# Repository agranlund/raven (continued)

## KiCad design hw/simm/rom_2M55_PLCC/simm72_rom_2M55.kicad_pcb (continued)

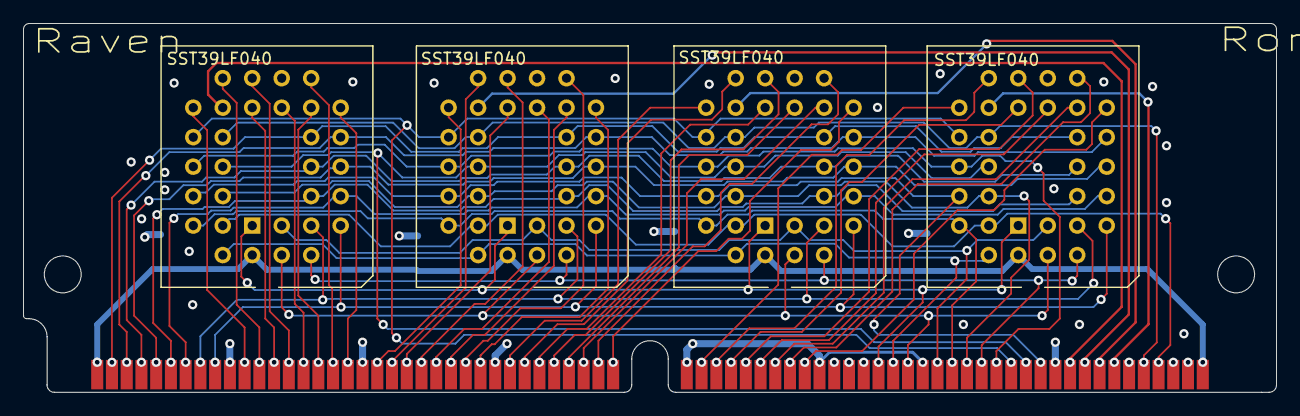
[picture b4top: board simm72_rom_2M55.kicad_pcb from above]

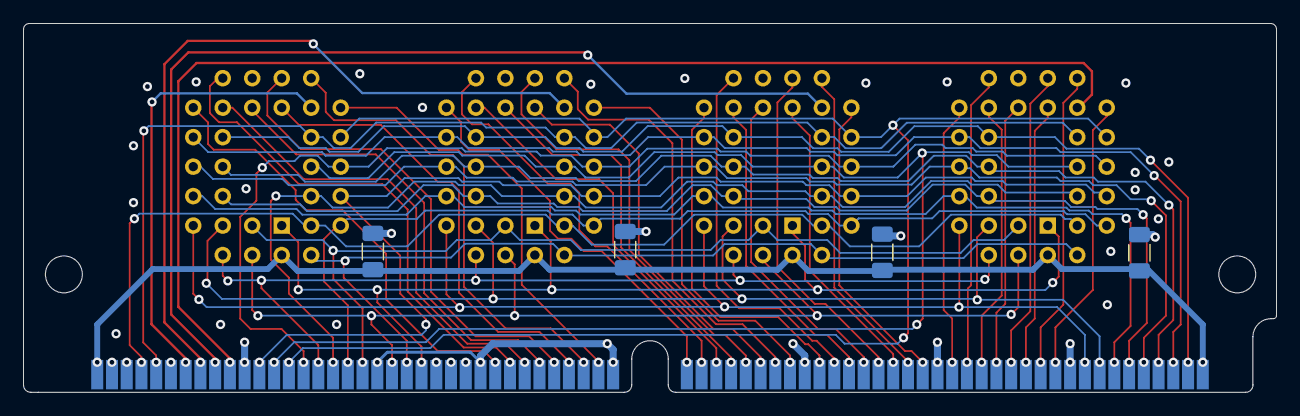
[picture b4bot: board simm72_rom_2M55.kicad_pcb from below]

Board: 4 copper layers, 108.0 x 31.8 mm, 9 parts (4 on the bottom side), 59 nets.

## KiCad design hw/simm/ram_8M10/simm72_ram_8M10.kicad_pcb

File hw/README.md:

All PCBs are designed within JLCPCB tolerances and Gerbers are exported for JLCPCB specifications.

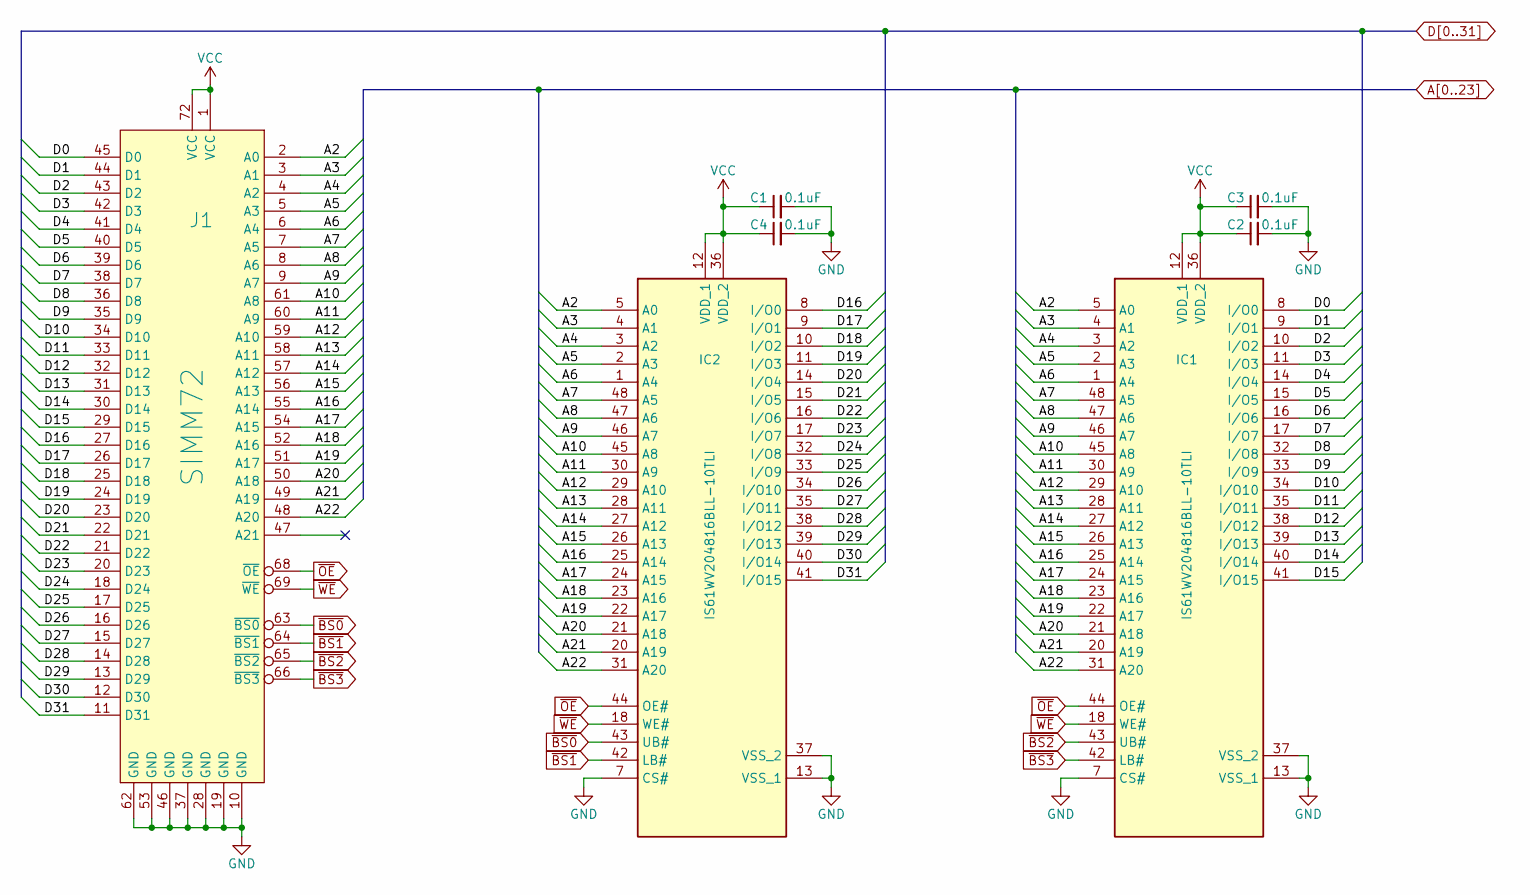
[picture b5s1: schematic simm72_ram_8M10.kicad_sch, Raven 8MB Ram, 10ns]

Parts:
C1, C2, C3, C4: 0.1uF; C_1206_3216Metric_Pad1.33x1.80mm_HandSolder; Manufacturer_Part_Number C1206C104K5RACTU
IC1, IC2: IS61WV204816BLL-10TLI; SOP50P2000X120-48N; Mouser Part Number 870-WV204816BLL10TLI
J1: SIMM72; SIMM72_edge

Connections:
A2: IC1.5 (A0), IC2.5 (A0), J1.2 (A0)
A3: IC1.4 (A1), IC2.4 (A1), J1.3 (A1)
A4: IC1.3 (A2), IC2.3 (A2), J1.4 (A2)
A5: IC1.2 (A3), IC2.2 (A3), J1.5 (A3)
A6: IC1.1 (A4), IC2.1 (A4), J1.6 (A4)
A7: IC1.48 (A5), IC2.48 (A5), J1.7 (A5)
A8: IC1.47 (A6), IC2.47 (A6), J1.8 (A6)
A9: IC1.46 (A7), IC2.46 (A7), J1.9 (A7)
A10: IC1.45 (A8), IC2.45 (A8), J1.61 (A8)
A11: IC1.30 (A9), IC2.30 (A9), J1.60 (A9)
A12: IC1.29 (A10), IC2.29 (A10), J1.59 (A10)
A13: IC1.28 (A11), IC2.28 (A11), J1.58 (A11)
A14: IC1.27 (A12), IC2.27 (A12), J1.57 (A12)
A15: IC1.26 (A13), IC2.26 (A13), J1.56 (A13)
A16: IC1.25 (A14), IC2.25 (A14), J1.55 (A14)
A17: IC1.24 (A15), IC2.24 (A15), J1.54 (A15)
A18: IC1.23 (A16), IC2.23 (A16), J1.52 (A16)
A19: IC1.22 (A17), IC2.22 (A17), J1.51 (A17)
A20: IC1.21 (A18), IC2.21 (A18), J1.50 (A18)
A21: IC1.20 (A19), IC2.20 (A19), J1.49 (A19)
A22: IC1.31 (A20), IC2.31 (A20), J1.48 (A20)
D0: IC1.8 (I/O0), J1.45 (D0)
D1: IC1.9 (I/O1), J1.44 (D1)
D2: IC1.10 (I/O2), J1.43 (D2)
D3: IC1.11 (I/O3), J1.42 (D3)
D4: IC1.14 (I/O4), J1.41 (D4)
D5: IC1.15 (I/O5), J1.40 (D5)
D6: IC1.16 (I/O6), J1.39 (D6)
D7: IC1.17 (I/O7), J1.38 (D7)
D8: IC1.32 (I/O8), J1.36 (D8)
D9: IC1.33 (I/O9), J1.35 (D9)
D10: IC1.34 (I/O10), J1.34 (D10)
D11: IC1.35 (I/O11), J1.33 (D11)
D12: IC1.38 (I/O12), J1.32 (D12)
D13: IC1.39 (I/O13), J1.31 (D13)
D14: IC1.40 (I/O14), J1.30 (D14)
D15: IC1.41 (I/O15), J1.29 (D15)
D16: IC2.8 (I/O0), J1.27 (D16)
D17: IC2.9 (I/O1), J1.26 (D17)
D18: IC2.10 (I/O2), J1.25 (D18)
D19: IC2.11 (I/O3), J1.24 (D19)
D20: IC2.14 (I/O4), J1.23 (D20)
D21: IC2.15 (I/O5), J1.22 (D21)
D22: IC2.16 (I/O6), J1.21 (D22)
D23: IC2.17 (I/O7), J1.20 (D23)
D24: IC2.32 (I/O8), J1.18 (D24)
D25: IC2.33 (I/O9), J1.17 (D25)
D26: IC2.34 (I/O10), J1.16 (D26)
D27: IC2.35 (I/O11), J1.15 (D27)
D28: IC2.38 (I/O12), J1.14 (D28)
D29: IC2.39 (I/O13), J1.13 (D29)
D30: IC2.40 (I/O14), J1.12 (D30)
D31: IC2.41 (I/O15), J1.11 (D31)
GND: C1.2, C2.2, C3.2, C4.2, IC1.7 (CS#), IC1.13 (VSS_1), IC1.37 (VSS_2), IC2.7 (CS#), IC2.13 (VSS_1), IC2.37 (VSS_2), J1.10 (GND), J1.19 (GND), J1.28 (GND), J1.37 (GND), J1.46 (GND), J1.53 (GND), J1.62 (GND)
VCC: C1.1, C2.1, C3.1, C4.1, IC1.12 (VDD_1), IC1.36 (VDD_2), IC2.12 (VDD_1), IC2.36 (VDD_2), J1.1 (VCC), J1.72 (VCC)
~BS0: IC2.43 (UB#), J1.63 (~BS0)
~BS1: IC2.42 (LB#), J1.64 (~BS1)
~BS2: IC1.43 (UB#), J1.65 (~BS2)
~BS3: IC1.42 (LB#), J1.66 (~BS3)
~OE: IC1.44 (OE#), IC2.44 (OE#), J1.68 (~OE)
~WE: IC1.18 (WE#), IC2.18 (WE#), J1.69 (~WE)

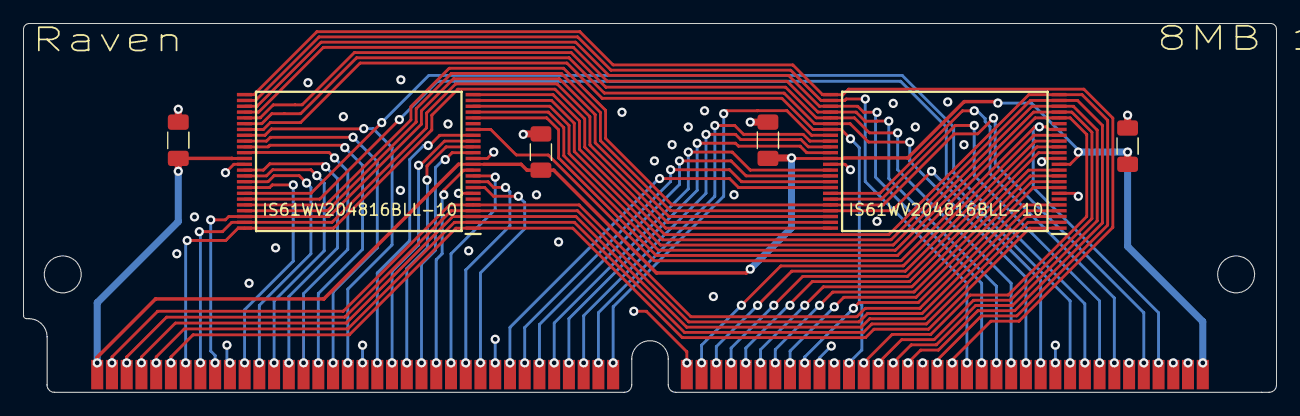
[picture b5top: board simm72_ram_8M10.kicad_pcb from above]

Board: 4 copper layers, 108.0 x 31.8 mm, 7 parts (0 on the bottom side), 61 nets.

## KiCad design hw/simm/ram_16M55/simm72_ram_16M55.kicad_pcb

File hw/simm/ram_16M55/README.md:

# RAM module: 16MB / 55ns

## BOM

| Manufacturer          | Part number                 | Value       | Count | Ref                                   |
|-----------------------|-----------------------------|-------------|-------|---------------------------------------|
| Alliance Memory       | AS6C6416-55TIN              | 16x4MBit    | 2     | IC1, IC2                              |
| Kemet                 | C1206C104K5RACTU            | 0.1u        | 2     | C1, C2                                |

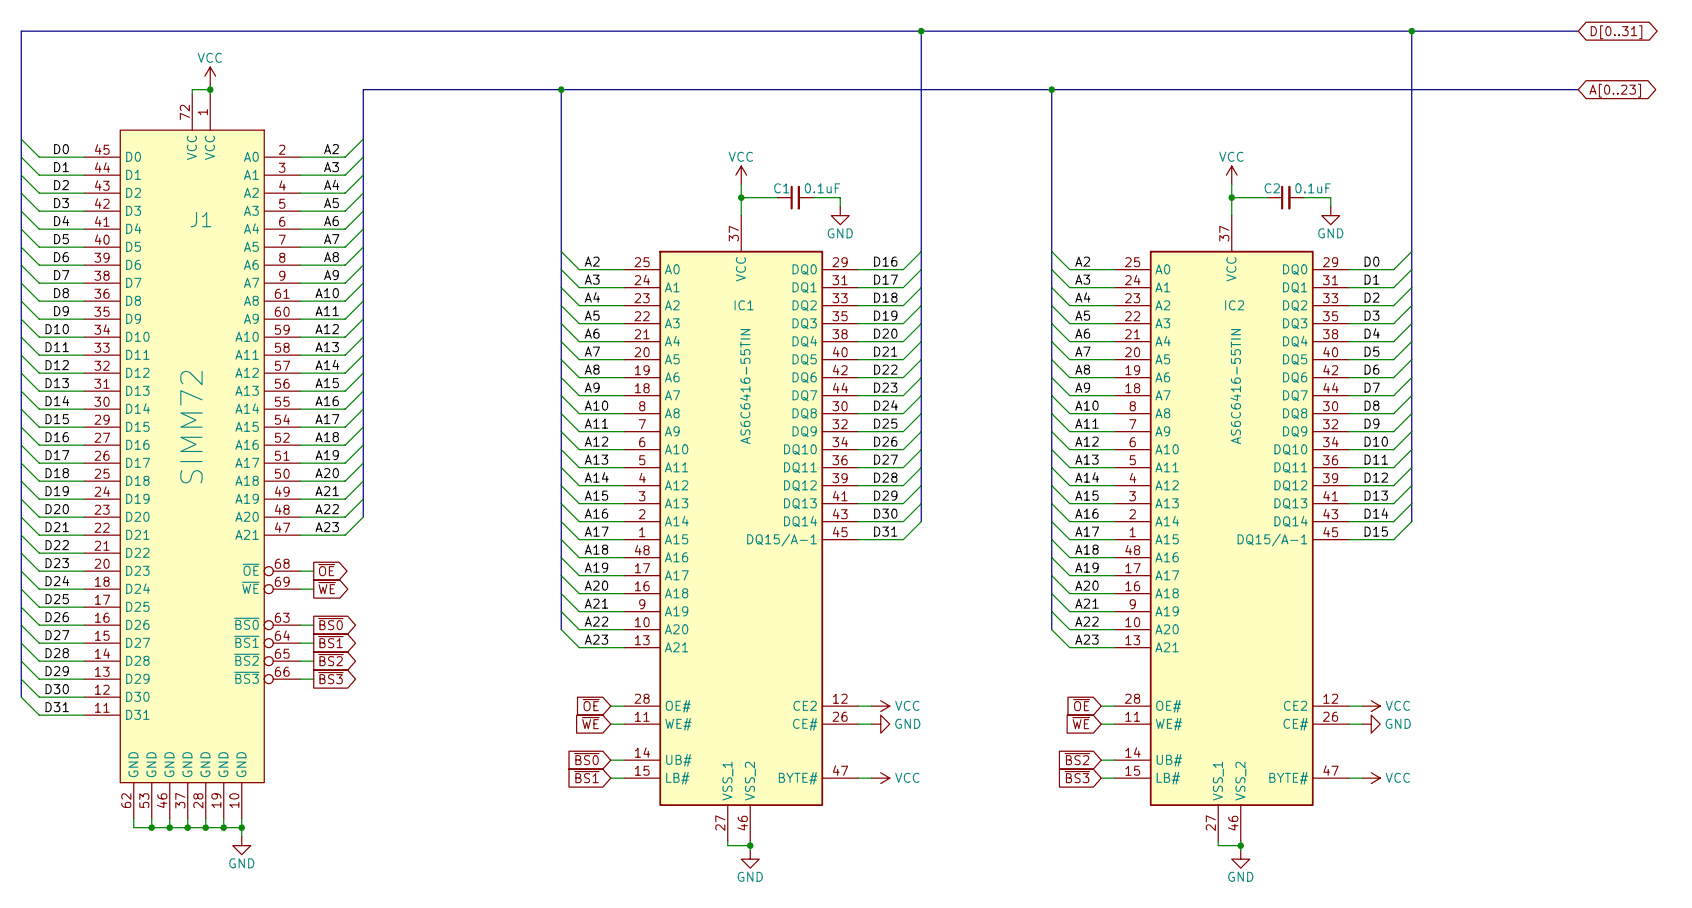
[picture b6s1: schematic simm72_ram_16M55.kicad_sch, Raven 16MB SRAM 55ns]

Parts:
C1, C2: 0.1uF; C_1206_3216Metric_Pad1.33x1.80mm_HandSolder; Manufacturer_Part_Number C1206C104K5RACTU
IC1, IC2: AS6C6416-55TIN; SOP50P2000X120-48N; Mouser Part Number 913-AS6C6416-55TIN
J1: SIMM72; SIMM72_edge

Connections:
A2: IC1.25 (A0), IC2.25 (A0), J1.2 (A0)
A3: IC1.24 (A1), IC2.24 (A1), J1.3 (A1)
A4: IC1.23 (A2), IC2.23 (A2), J1.4 (A2)
A5: IC1.22 (A3), IC2.22 (A3), J1.5 (A3)
A6: IC1.21 (A4), IC2.21 (A4), J1.6 (A4)
A7: IC1.20 (A5), IC2.20 (A5), J1.7 (A5)
A8: IC1.19 (A6), IC2.19 (A6), J1.8 (A6)
A9: IC1.18 (A7), IC2.18 (A7), J1.9 (A7)
A10: IC1.8 (A8), IC2.8 (A8), J1.61 (A8)
A11: IC1.7 (A9), IC2.7 (A9), J1.60 (A9)
A12: IC1.6 (A10), IC2.6 (A10), J1.59 (A10)
A13: IC1.5 (A11), IC2.5 (A11), J1.58 (A11)
A14: IC1.4 (A12), IC2.4 (A12), J1.57 (A12)
A15: IC1.3 (A13), IC2.3 (A13), J1.56 (A13)
A16: IC1.2 (A14), IC2.2 (A14), J1.55 (A14)
A17: IC1.1 (A15), IC2.1 (A15), J1.54 (A15)
A18: IC1.48 (A16), IC2.48 (A16), J1.52 (A16)
A19: IC1.17 (A17), IC2.17 (A17), J1.51 (A17)
A20: IC1.16 (A18), IC2.16 (A18), J1.50 (A18)
A21: IC1.9 (A19), IC2.9 (A19), J1.49 (A19)
A22: IC1.10 (A20), IC2.10 (A20), J1.48 (A20)
A23: IC1.13 (A21), IC2.13 (A21), J1.47 (A21)
D0: IC2.29 (DQ0), J1.45 (D0)
D1: IC2.31 (DQ1), J1.44 (D1)
D2: IC2.33 (DQ2), J1.43 (D2)
D3: IC2.35 (DQ3), J1.42 (D3)
D4: IC2.38 (DQ4), J1.41 (D4)
D5: IC2.40 (DQ5), J1.40 (D5)
D6: IC2.42 (DQ6), J1.39 (D6)
D7: IC2.44 (DQ7), J1.38 (D7)
D8: IC2.30 (DQ8), J1.36 (D8)
D9: IC2.32 (DQ9), J1.35 (D9)
D10: IC2.34 (DQ10), J1.34 (D10)
D11: IC2.36 (DQ11), J1.33 (D11)
D12: IC2.39 (DQ12), J1.32 (D12)
D13: IC2.41 (DQ13), J1.31 (D13)
D14: IC2.43 (DQ14), J1.30 (D14)
D15: IC2.45 (DQ15/A-1), J1.29 (D15)
D16: IC1.29 (DQ0), J1.27 (D16)
D17: IC1.31 (DQ1), J1.26 (D17)
D18: IC1.33 (DQ2), J1.25 (D18)
D19: IC1.35 (DQ3), J1.24 (D19)
D20: IC1.38 (DQ4), J1.23 (D20)
D21: IC1.40 (DQ5), J1.22 (D21)
D22: IC1.42 (DQ6), J1.21 (D22)
D23: IC1.44 (DQ7), J1.20 (D23)
D24: IC1.30 (DQ8), J1.18 (D24)
D25: IC1.32 (DQ9), J1.17 (D25)
D26: IC1.34 (DQ10), J1.16 (D26)
D27: IC1.36 (DQ11), J1.15 (D27)
D28: IC1.39 (DQ12), J1.14 (D28)
D29: IC1.41 (DQ13), J1.13 (D29)
D30: IC1.43 (DQ14), J1.12 (D30)
D31: IC1.45 (DQ15/A-1), J1.11 (D31)
GND: C1.2, C2.2, IC1.26 (CE#), IC1.27 (VSS_1), IC1.46 (VSS_2), IC2.26 (CE#), IC2.27 (VSS_1), IC2.46 (VSS_2), J1.10 (GND), J1.19 (GND), J1.28 (GND), J1.37 (GND), J1.46 (GND), J1.53 (GND), J1.62 (GND)
VCC: C1.1, C2.1, IC1.12 (CE2), IC1.37 (VCC), IC1.47 (BYTE#), IC2.12 (CE2), IC2.37 (VCC), IC2.47 (BYTE#), J1.1 (VCC), J1.72 (VCC)
~BS0: IC1.14 (UB#), J1.63 (~BS0)
~BS1: IC1.15 (LB#), J1.64 (~BS1)
~BS2: IC2.14 (UB#), J1.65 (~BS2)
~BS3: IC2.15 (LB#), J1.66 (~BS3)
~OE: IC1.28 (OE#), IC2.28 (OE#), J1.68 (~OE)
~WE: IC1.11 (WE#), IC2.11 (WE#), J1.69 (~WE)

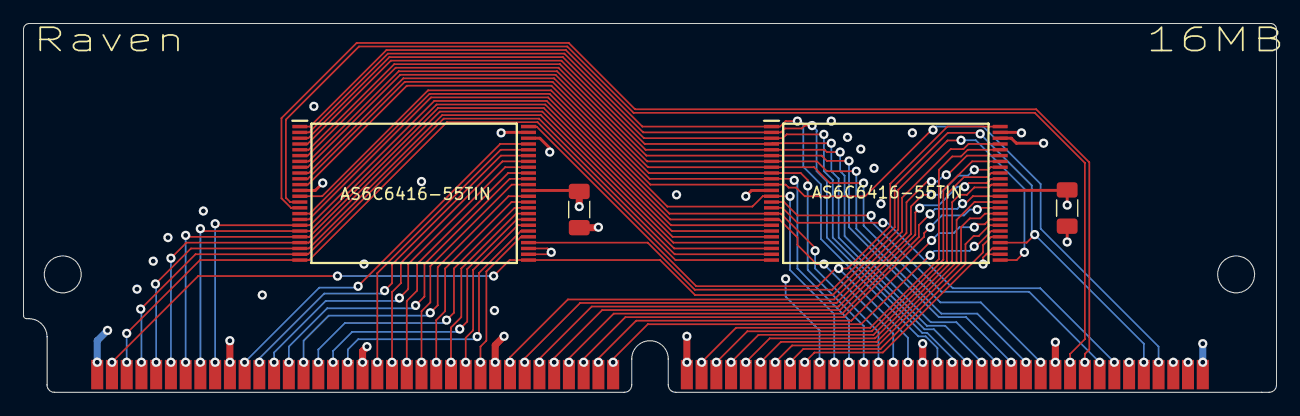
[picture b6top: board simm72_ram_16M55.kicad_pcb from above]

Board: 4 copper layers, 108.0 x 31.8 mm, 5 parts (0 on the bottom side), 62 nets.

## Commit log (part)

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2026-02-14 debugprint refactor
2026-02-14 rvnova tools
2026-02-14 tiny cleanups
2026-02-14 Update ISA graphics card requirements in README
    Expanded ISA graphics card section with hardware acceleration details.
2026-02-14 Create makefile
2026-02-15 rvnova settings
    - added rvga.inf settings file
    - remove w32i interleave option from rvbios
    - rename default driver to svga
    - use generated bibs for svga driver
2026-02-15 setaddr fix for < GD5426
2026-02-15 fix compile error in debug
2026-02-15 wip tseng driver (disabled)
2026-02-15 wip tseng driver enabled
2026-02-15 v_bar vdi accel can now compile again
    did some tests, still not working in 100% scenarios. keep disabled.
2026-02-16 Add Blender 3D IO Shield file
    add Blender 3D file used to create IO Shield STL
2026-02-16 tseng fixes
    - correctly place W32i LFB address
    - detect clocks for custom resolutions
    - 1280x720 works and tested on AX and W32i
2026-02-17 tseng: use vgabios to set refresh rate when supported
2026-02-17 rvnova : accelerate v_bar primitive
2026-02-18 hardware accelerate vt_clear_rows
2026-02-23 rvga: build for 020+
2026-02-23 WDC reduce blitter call overhead
2026-02-23 Cirrus: reduce blitter call overhead
    - reduce redundant register writes
    - use mmio on GD5429+
    - use polyfill capabilities on GD5429+
2026-02-23 additional vdi acceleration
    - vt52 clear rows
    - general VDI primitives accelerated with naive blitter hlines
2026-02-23 cirrus: pattern fill fix
2026-02-23 remove a bunch of temp comments
2026-02-25 don't force 8x8 terminal font
    was causing issues with nova vdi
2026-02-25 wip trapezoid testing
2026-02-25 Update graphics card hardware acceleration details
2026-02-28 cirrus: fixed bad pattern address
    was setting wrong address on gpu side.
    worked by accident because the 2MB offset was either ignored or wrapped.
2026-02-28 rasterize speed tests
2026-03-02 option to scale dac value
    handle settings in main and pass it to each driver on init
2026-03-02 correct fillpattern addr
2026-03-04 S3 driver, small fixes
2026-03-08 uip: fixed stringop warnings
2026-03-08 uip: support 16bit dma
2026-03-08 rvnova: graceful exit if required files cannot be found
    instead of crashing if selected driver files cannot be loaded, or other required files.
2026-03-08 changed default desk resolution
    Standard 640x480x16color as default if nothing was selected yet
2026-03-08 fixed bib generator pitch bug
2026-03-10 w32 accel preparations
2026-03-28 mintelf gcc 15.2.0
    - updated libcmini
    - using only mintelf for gcc now
2026-03-28 mintelf gcc 15.2.0
2026-03-28 ability to use registers as value for d and a commands
2026-03-30 add memmove to bootrom stdlib
2026-03-30 bootrom fixes and optimisations
    - export func to reinstall 060sp in TOS vectors
    - heap area automatically sized by linkedscript
    - misc performance optimisations
2026-03-30 install 060sp in TOS vectors
    installed by bootrom in hidden vbr proxy by default.
    this moves it to TOS vectors at $0
    required for some programs to correctly identify 040 vs 060 (eg. Mint 1.16.0)
2026-03-31 fix crash on unassigned interrupt vectors
2026-03-31 delayus todo comment
2026-03-31 cache
2026-03-31 Squashed 'sw/rom/emutos/' changes from 65a71f38e3..67e4a4cd1b
    67e4a4cd1b Speed up hard disk check again
    cebdff8972 Hatari test: Allow more time to reach Desktop
    e095c950ab Fix 'dmaboot' for ColdFire architecture
    32ddba4141 Update copyright years
    d5bc81e9c3 Remove obsolete disabled code
    590636a4f1 Run cartridge applications before harddisk boot
2026-04-03 Squashed 'sw/rom/emutos/' changes from 67e4a4cd1b..f96a524ca4
    f96a524ca4 Harden GEMDOS media change error handling
    git-subtree-dir: sw/rom/emutos
    git-subtree-split: f96a524ca4125b44c46bd9833ee288955cfbf79a
2026-04-03 update release notes
    show only latest changes in github history.
    include full release history as textfile in package.
2026-04-03 fix blitter/cache menu out of sync if no emudesk.inf was present
2026-04-03 add get_cache function
2026-04-03 fix cache menu item out of sync with reality
2026-04-03 disable cache for certain auto programs
    todo: move this to rvbios.prg instead of inside emutos
2026-04-04 rvbios cleanup
2026-04-04 simplified cacr helpers
2026-04-04 safer 060sp reinstall
2026-04-04 remove unnecessary nops
2026-04-04 isa_bios delayus helper and version bump
2026-04-04 print version on startup
2026-04-04 include info for xcontrol
2026-04-04 include ct60 version of xcontrol
2026-04-04 clear st-ram before launching tos
2026-04-05 Revert "disable cache for certain auto programs"
    This reverts commit e22a2c34352b3080157ce5dacf676213542e2d44.
2026-04-05 add comments
2026-04-05 comments
2026-04-05 applying cache setting from emudesk follow same logic as blitter
2026-04-05 support xbios puntaes
2026-04-05 remove unnecessary patch_xc.prg
2026-04-06 support old version ct60 xbios
2026-04-06 updated dist readmes
2026-04-06 fixed boot message corruption
2026-04-06 include gsxbmixer in dist
2026-04-06 bump version numbers
2026-04-06 release notes
2026-04-06 readded nops because it can't hurt
2026-04-08 fix nova setup when no drivers are present
2026-04-08 copyright dates
2026-04-08 better detect full vs tsr-only mode
2026-04-08 tos extension cartridge (rvbios in rom)
2026-04-08 rvbios in rom
    mounting a virtual cartridge, able to hook at various points during TOS init.
    rvbios runs just before auto programs loads.
2026-04-08 makefile fixes
2026-04-10 increase i2c delay
    shot in the dark trying to hunt down intermittent nvram read-failure.
2026-04-10 restart computer after ckbd firmware flashing
2026-04-10 minor verify before flashing rom/ckbd
    naive, proper checksum test should be written.
2026-04-10 fix ckbd version readout
2026-04-10 dev define for testing setup gui
2026-04-10 setup gui additions
    - rearranged tab order
    - added skeleton for debug tab
    - cleaned up system tab
    - added rom + kbd flash functionality to system tab
2026-04-11 support larger pram area in rom
2026-04-11 wip pram + flash fixes
2026-04-11 add pram command to monitor
2026-04-11 cleanup
2026-04-11 store initial baudrate in pram
2026-04-11 cosmetic
2026-04-11 cosmetic bugfix
2026-04-11 don't update flash if value didn't change
2026-04-11 version
2026-04-12 cfg's now using pram instead of rtc-nvram
2026-04-12 comment about potential pitfall with cfgs
2026-04-19 Update PicoGus from original source and PGUSINIT v3.9.0a for Raven
    Update PicoGUS source code and compile PGUSINIT.PRG v3.9.0a for use with v4.0.0 firmware
2026-04-22 kicad lib updates
2026-04-22 add datasheet for dsp56303
2026-04-22 A2 rework
    - reworking top-left area for dsp56303
    - internal speaker header for YM
    - software controlled volume for YM
    - misc routing cleanup
2026-04-23 A2. YM:IOA7 used for detecting volume+spkr controls
2026-04-24 A2: DSP ram routing
2026-04-24 a2, reannotate
2026-04-26 more a2 wip
2026-04-27 A2: DAC for DSP and mix with YM
2026-04-29 A2: simplified DSP RAM connection
    AA0 -> SRAM_CE
    AA1 -> SRAM_A16
    OMR register must be set to priority encoding disabled.
2026-04-29 A2: fixed comment about DSP ram memory map
2026-05-02 Document errors to consider when building
    Added error notes regarding capacitor orientation and silkscreen labeling for J305.
2026-05-02 A2: dac + adc + dsp work
2026-05-03 A2 wip
    audio hooked up
    added caps for fan headers
2026-05-03 A2: changed oscillator caps
    also fixed reference identifier
2026-05-07 PGUSINIT.PRG v3.9.0a updates for firmware v4.1.0 and above
    -SB: finalize IRQ/DMA/options settings
    -PGUSINIT: Update to work with Firmware v4.1.0 and above
    -PicoGUS Readme: Add OPL types back to README
2026-05-22 misc a2 work
2026-05-23 A2: routed few misc signals
    temp1, temp2, argb, pwm, pwrsw
    remove uart irq from mfp1, was unused in A1 anyway.
    (uart irq was always at avec5)
2026-05-23 A2 routing
2026-05-24 A2: schema + routing complete. ERC + DRC complete.
    Let sit for a while, revisit and sanity check with fresh eyes before gerber.
    Todo: double check BOM export and fix missing infos if any.
2026-05-25 readme
2026-05-28 A2: cosmetics and bom preparations
2026-05-28 Update README with BOM and fix details
2026-05-28 A2: bom
2026-05-28 A2: bom files
2026-05-29 A2: cleaned up fab layer
2026-05-29 fix: add buffer-length check in IspCmdTool.cpp
    Multiple sprintf calls write formatted strings into fixed-size stack buffers (szStr, TextBufferTmp) without bounds checking
2026-05-29 A2: minor clarifications
2026-05-30 A2: gerber settings and misc
2026-05-30 A2 gerber export
2026-05-31 removed unused components fields
2026-05-31 a2 clean and reexport
2026-05-31 A2: dsp jtag
    resistor on TCK instead of hardwired.
    makes it possible, but uncomfortable, to jtag by placing needles directly on chip.
2026-05-31 A2 mouser bom
2026-06-02 A2: notes about replacing ADI parts
2026-06-07 rvsnd: fix midi xbios crash
2026-06-20 pwr and gnd netclass colors
2026-06-20 netclass colors
2026-06-20 ARGB header note
2026-06-20 Rename 'Errata' section to 'Notes and Errata'
2026-06-20 Update README with corrected wording for ARGB header
2026-06-21 replaced a couple of caps
2026-06-25 a2: powerswitch pin
2026-06-27 rom: identify board rev at boot
2026-06-27 a2 memory map
2026-06-27 uiptool: fixed ftp server uninitialized variable in protothread
2026-06-27 minor release note cleanup
2026-06-27 Revise README with component changes and notes
    Updated README with recent fixes and additions.
2026-06-27 removed PWR_SW to UART:RI connection
2026-06-27 ckbd: default 125000 baud on rev.a2
2026-06-27 rom: fast fixed ckbd baudrate on a2
2026-06-28 srec: improve selftest
2026-06-28 moved a1 upgrade hw into a1 folder
2026-06-28 Clarify PWR_SW trace cut note in README
    Updated note about PWR_SW to UART:RI trace cut and reflected changes in GitHub schematic.
2026-06-28 Revise status and notes in README.md
    Updated README to reflect testing phase and corrected wording.
2026-06-28 import nessi a2 firmware
2026-06-28 emutos: flush IKBD fifo on boot
2026-06-28 renamed uart gpo1
2026-06-28 uart1:ria to gnd, same as A1
2026-06-28 ckbd: fix cpu temp readout
2026-06-28 rom: minor ikbd cleanup
2026-06-30 rom: reverse hw polarity of ym:porta:bit6
    matching Falcon behaviour for speaker mute/unmute
